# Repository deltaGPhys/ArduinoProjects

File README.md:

# ArduinoProjects
Assorted Arduino projects

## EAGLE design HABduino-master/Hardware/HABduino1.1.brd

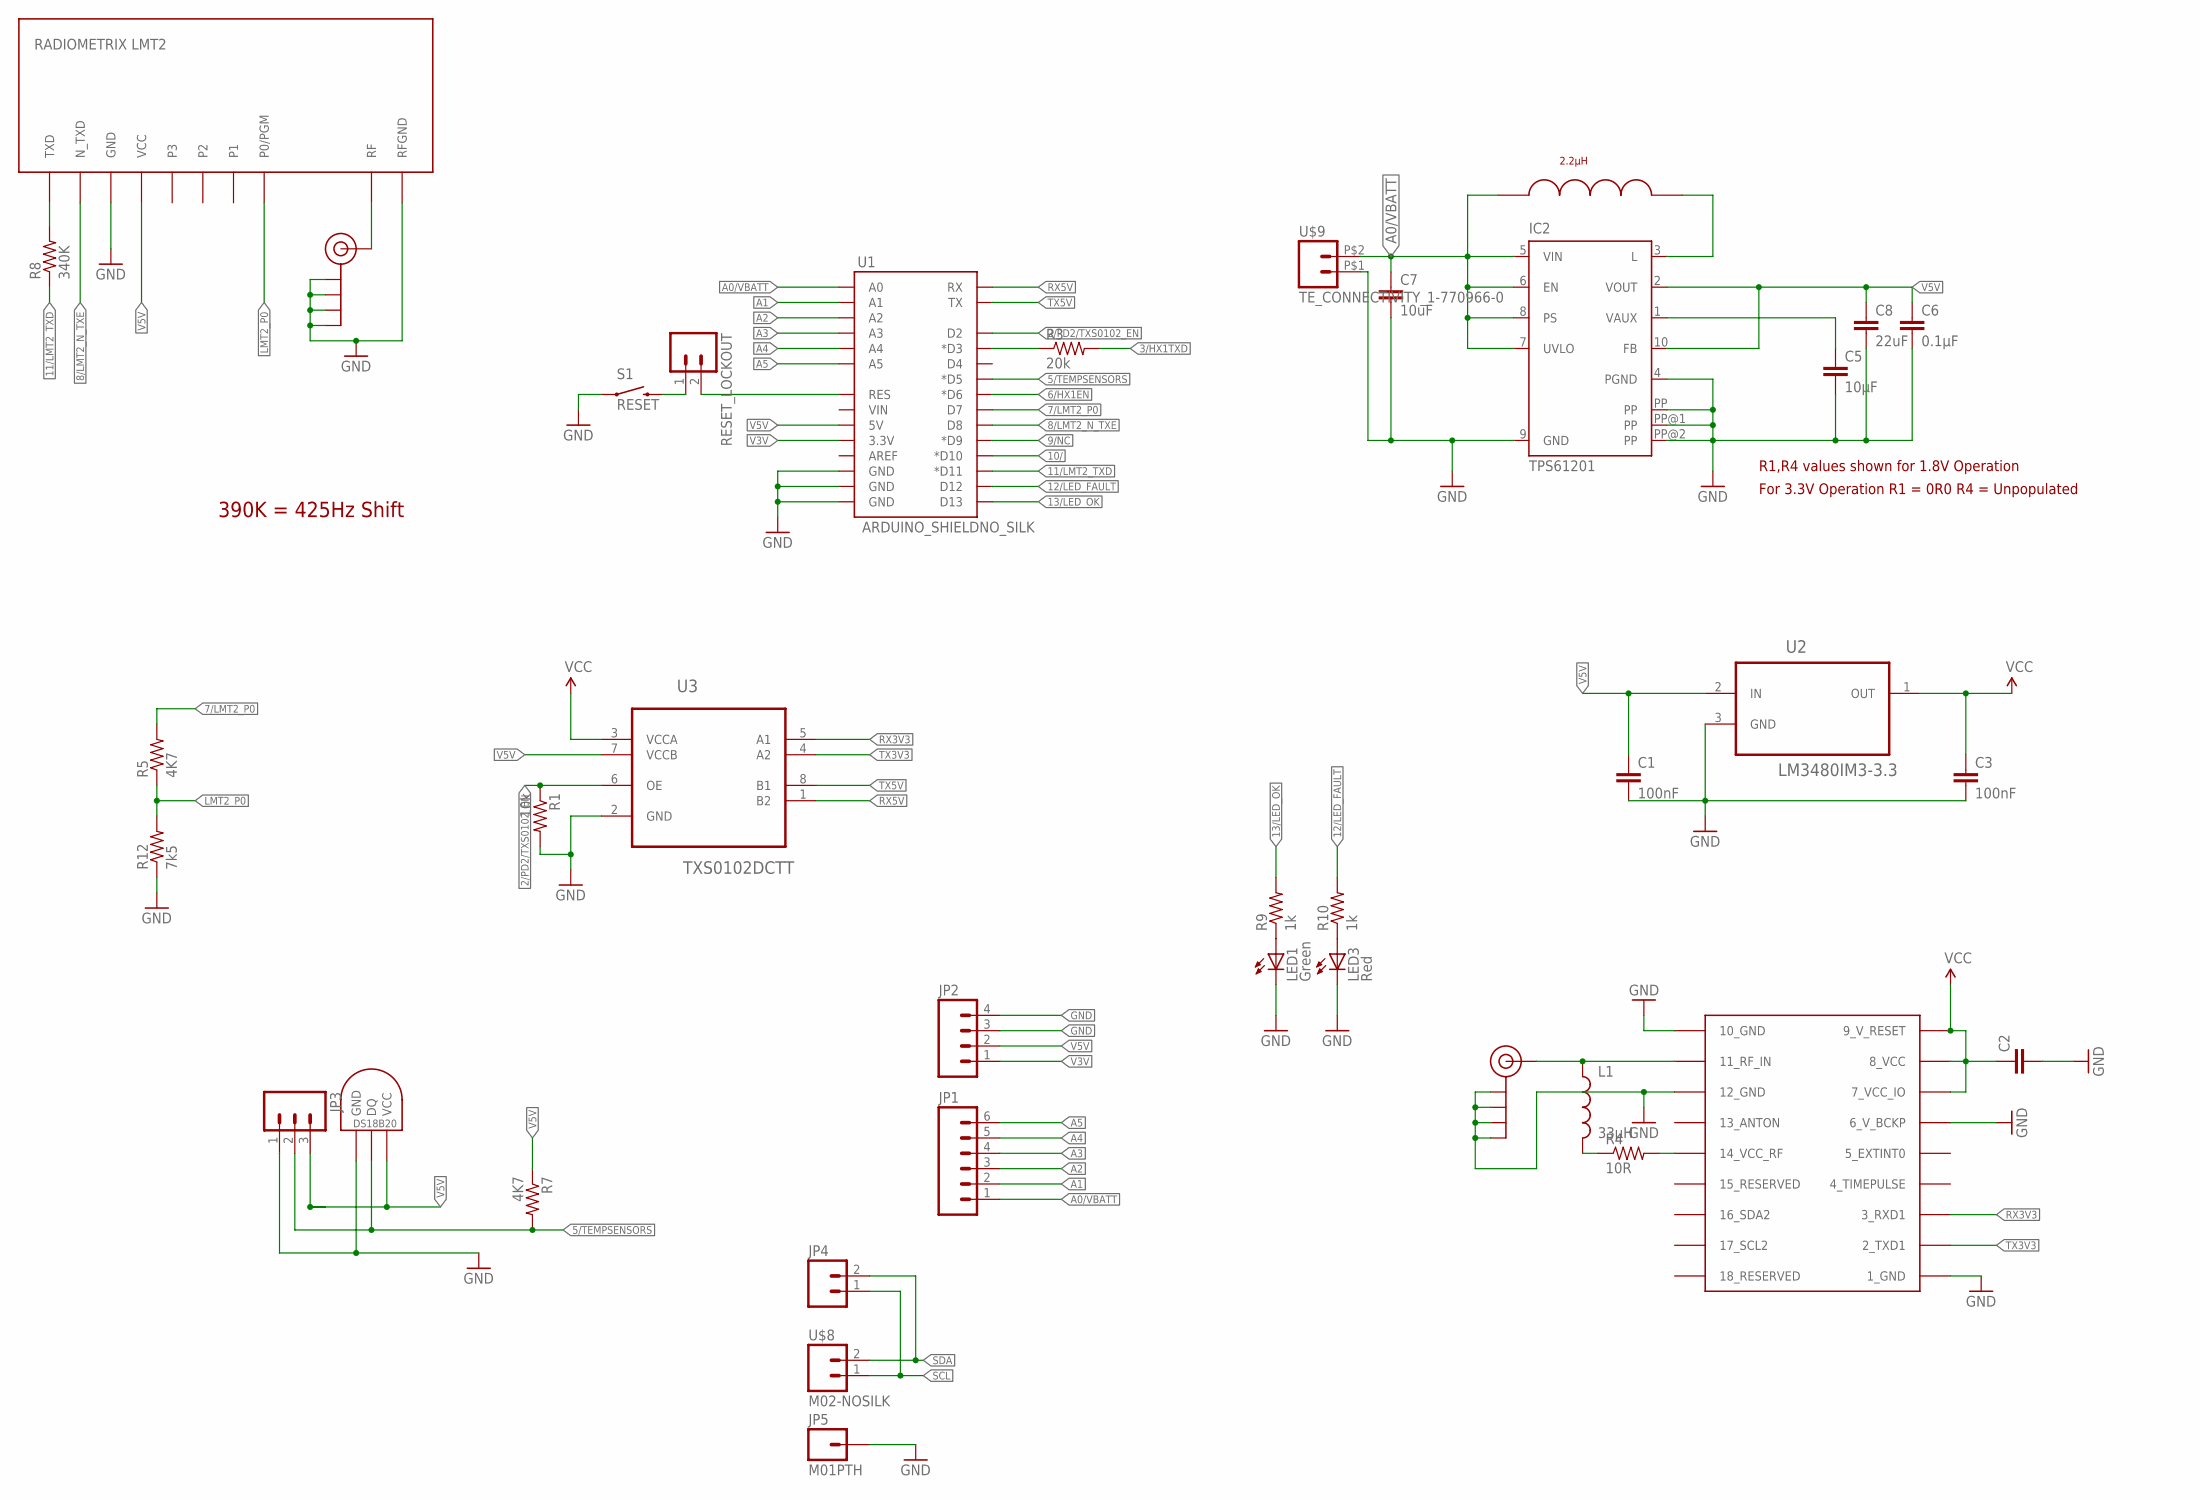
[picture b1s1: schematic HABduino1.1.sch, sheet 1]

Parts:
C1, C3: 100nF; 0603-CAP
C2: CAP0603-CAP; 0603-CAP
C5: 10µF; 0603-CAP
C6: 0.1µF; 0603-CAP
C7: 10uF; 1206
C8: 22uF; 1206
IC2: TPS61201; S-PDSO-N10
J$1, J$2: SMA_EDGE; SMA-EDGE
JP1: M06SIP; 1X06
JP2: M04PTH; 1X04
JP3: M03PTH; 1X03
JP4: M02PTH; 1X02
JP5: M01PTH; 1X01
L1: 33µH; 0603
LED1: Green; LED-0603
LED3: Red; LED-0603
R1: 10k; 0603-RES
R3: 20k; 0603-RES
R4: 10R; 0603-RES
R5, R7: 4K7; 0603-RES
R8: 340K; 0603-RES
R9, R10: 1k; 0603-RES
R12: 7k5; 0603-RES
RESET_LOCKOUT: M02PTH; 1X02
S1: RESET; TACTILE_SWITCH_TALL
TEMPINT: DS1821; DS1820
U1: ARDUINO_SHIELDNO_SILK; DUEMILANOVE_VIAS
U2: LM3480IM3-3.3; SOT95P251X112-3N
U3: TXS0102DCTT; SOP65P400X130-8N
U$1: UBLOX_MAX-6
U$2: RADIOMETRIX_LMT2; RADIOMETRIX-LMT2
U$8: M02-NOSILK
U$9: TE_CONNECTIVITY_1-770966-0; FARNELL 1098556
U$10: 2.2µH; COILCRAFT_LPS4018

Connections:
2/PD2/TXS0102_EN: R1.1, U1.D2, U3.6 (OE)
3/HX1TXD: R3.2; also elsewhere on the board
5/TEMPSENSORS: JP3.2, R7.2, TEMPINT.DQ, U1.D5 (*D5)
6/HX1EN: U1.D6 (*D6); also elsewhere on the board
7/LMT2_P0: R5.2, U1.D7
8/LMT2_N_TXE: U1.D8, U$2.N_TXE (N_TXD)
9/NC: U1.D9 (*D9)
10/: U1.D10 (*D10)
11/LMT2_TXD: R8.1, U1.D11 (*D11)
12/LED_FAULT: R10.2, U1.D12
13/LED_OK: R9.2, U1.D13
A0/VBATT: C7.1, IC2.5 (VIN), IC2.6 (EN), IC2.7 (UVLO), IC2.8 (PS), JP1.1, U1.A0, U$9.P$2 (2), U$10.P$1
A1: JP1.2, U1.A1
A2: JP1.3, U1.A2
A3: JP1.4, U1.A3
A4: JP1.5, U1.A4
A5: JP1.6, U1.A5
GND: C1.2, C2.2, C3.2, C5.2, C6.2, C7.2, C8.2, IC2.4 (PGND), IC2.9 (GND), IC2.PP, IC2.PP@1 (PP), IC2.PP@2 (PP), J$1.GND@0 (GND), J$1.GND@1 (GND), J$1.GND@2 (GND), J$1.GND@3 (GND), J$2.GND@0 (GND), J$2.GND@1 (GND), J$2.GND@2 (GND), J$2.GND@3 (GND), JP2.3, JP2.4, JP3.1, JP5.1, LED1.C, LED3.C, R1.2, R12.1, S1.A2 (1), TEMPINT.GND, U1.GND@0 (GND), U1.GND@1 (GND), U1.GND@2 (GND), U2.3 (GND), U3.2 (GND), U$1.1_GND, U$1.6_V_BCKP, U$1.10_GND, U$1.12_GND, U$2.GND, U$2.RFGND, U$9.P$1 (1); also elsewhere on the board
LMT2_P0: R5.1, R12.2, U$2.P0/PGM
unnamed: R3.1, U1.D3 (*D3)
unnamed: J$1.SIG (SIGNAL), U$2.RF
unnamed: J$2.SIG (SIGNAL), L1.1, U$1.11_RF_IN
unnamed: IC2.3 (L), U$10.P$2
unnamed: RESET_LOCKOUT.1, S1.B2 (2)
unnamed: RESET_LOCKOUT.2, U1.RES
unnamed: C5.1, IC2.1 (VAUX)
unnamed: LED1.A, R9.1
unnamed: LED3.A, R10.1
unnamed: L1.2, R4.1
unnamed: R4.2, U$1.14_VCC_RF
RX3V3: U3.5 (A1), U$1.3_RXD1
RX5V: U1.RX, U3.1 (B2)
SCL: JP4.1, U$8.1
SDA: JP4.2, U$8.2
TX3V3: U3.4 (A2), U$1.2_TXD1
TX5V: U1.TX, U3.8 (B1)
V3V: JP2.1, U1.3.3V
V5V: C1.1, C6.1, C8.1, IC2.2 (VOUT), IC2.10 (FB), JP2.2, JP3.3, R7.1, TEMPINT.VDD (VCC), U1.5V, U2.2 (IN), U3.7 (VCCB), U$2.VCC; also elsewhere on the board
VCC: C2.1, C3.1, U2.1 (OUT), U3.3 (VCCA), U$1.7_VCC_IO, U$1.8_VCC, U$1.9_V_RESET
_LMT2TXD: R8.2, U$2.TXD

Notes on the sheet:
390K = 425Hz Shift
R1,R4 values shown for 1.8V Operation
For 3.3V Operation R1 = 0R0 R4 = Unpopulated

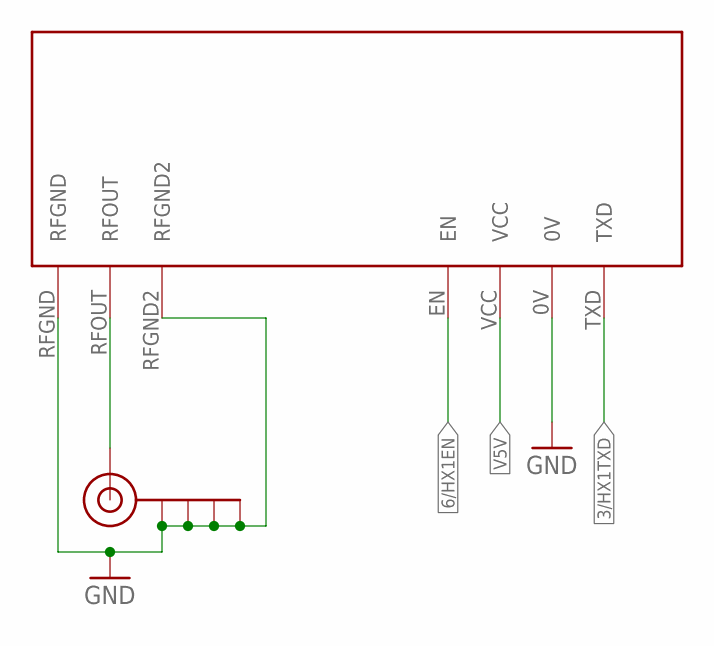
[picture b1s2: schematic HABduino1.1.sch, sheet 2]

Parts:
J$3: SMA_EDGE; SMA-EDGE
U$7: RADIOMETRIX-HX1

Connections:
3/HX1TXD: U$7.TXD; also elsewhere on the board
6/HX1EN: U$7.EN; also elsewhere on the board
GND: J$3.GND@0 (GND), J$3.GND@1 (GND), J$3.GND@2 (GND), J$3.GND@3 (GND), U$7.0V, U$7.RFGND, U$7.RFGND2; also elsewhere on the board
unnamed: J$3.SIG (SIGNAL), U$7.RFOUT
V5V: U$7.VCC; also elsewhere on the board

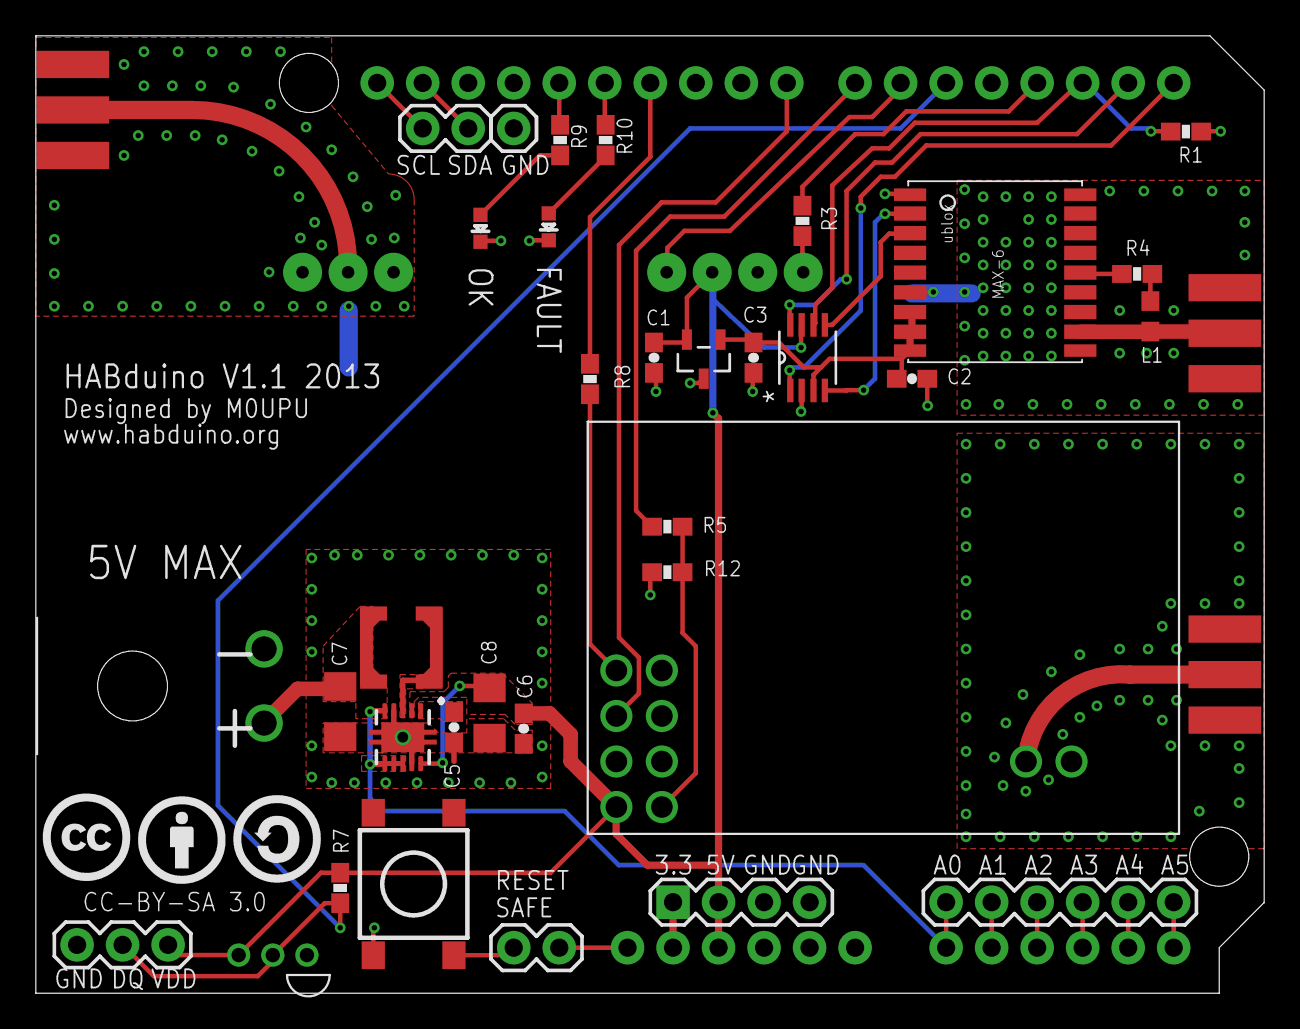
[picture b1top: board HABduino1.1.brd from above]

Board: 2 copper layers, 68.5 x 53.4 mm, 43 parts (1 on the bottom side), 39 nets.

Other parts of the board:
U$3: CC
U$5: CC-BY-21
U$6: CC-SA-21

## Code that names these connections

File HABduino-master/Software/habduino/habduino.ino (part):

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#define TXDELAY 0        // Delay between sentence TX's
#define RTTY_BAUD 50     // RTTY Baud rate (Recommended = 50)
#define LED_WARN 12
#define LED_OK 13
#define BATTERY_ADC A0
#define LMT2_SHIFT 500        
#define LMT2_OFFSET 0          // 0-100 Slightly adjusts the frequency by increasing the PWM 
#define LMT2_TXD 11
#define LMT2_ENABLE 8


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uint8_t buf[60]; 
uint8_t lock =0, sats = 0, hour = 0, minute = 0, second = 0;
uint8_t oldhour = 0, oldminute = 0, oldsecond = 0;
int GPSerror = 0,navmode = 0,psm_status = 0,lat_int=0,lon_int=0,tempsensors,temperature1=0,temperature2=0;
int32_t lat = 0, lon = 0, alt = 0, maxalt = 0, lat_dec = 0, lon_dec =0 ,tslf=0;
unsigned long currentMillis;
long previousMillis = 0;
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

void setup()  { 
  pinMode(LMT2_TXD, OUTPUT);
  pinMode(LED_WARN, OUTPUT);
  pinMode(HX1_ENABLE, OUTPUT);
  pinMode(LED_OK,OUTPUT);
  pinMode(LMT2_ENABLE, OUTPUT);
  pinMode(GPS_ON, OUTPUT);
  pinMode(BATTERY_ADC, INPUT);
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
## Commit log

2020-01-26 initial

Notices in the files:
HABduino-master/Software/habduino/habduino.ino:
This program is free software: you can redistribute it and/or modify
it under the terms of the GNU General Public License as published by
the Free Software Foundation, either version 3 of the License, or
(at your option) any later version.
The hardware design & code for Habduino is released under a Creative Commons License 3.0 Attribution-ShareAlike License :
See : http://creativecommons.org/licenses/by-sa/3.0
HABduino-master/Hardware/HABduino1.1.brd:
CC-BY-SA 3.0
Released under the Creative Commons Attribution Share-Alike 3.0 License
